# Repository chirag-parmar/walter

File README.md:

# Walter: The Water Butler

> Proof of concept document can be found [here](docs/POC.md)

### Dependencies: *(Tested on MACOS)*

1. [Download](https://www.nordicsemi.com/Software-and-tools/Software/nRF5-SDK/Download) nRF5 SDK
2. [Download](https://developer.arm.com/tools-and-software/open-source-software/developer-tools/gnu-toolchain/gnu-rm/downloads) ARM GCC toolchain
4. [Download](https://www.nordicsemi.com/Software-and-Tools/Development-Tools/nRF-Command-Line-Tools/Download#infotabs) nRF5x Command Line Tools.
4. Extract nRF5 SDK and rename the extracted folder to `nrf5-sdk`.
5. Extract GCC ARM toolchain and rename the extracted folder to `arm-toolchain`
6. Extract `nRF5x Command Line Tools` TAR file.
    * Navigate inside the nrf ommand line tools folder and install the Jlink package withing it.
    * Navigate inside the nrf ommand line tools folder and install the `nRF5x Command Line Tools` package withing it.
7. Check installations
    * J-Link *(MAC-OS)*: Check if this path exists `/Applications/SEGGER/JLink`
    * nRF5x Command Line Tools: `nrfjprog -v` must output the version.
8. Export Environment variables to specifying SDK folder path and ARM toolchain path.
    * `export SDK_ROOT=<PATH TO nrf5-sdk/ folder>`
    * `export GNU_INSTALL_ROOT=<PATH TO arm-toolchain/bin/ folder>`

> MAC-OS Complications: The system is going to complain that "the developer cannot be verified" for `arm-none-eabi-gcc`, `cc1`, `as`, `collect2`, `ld`, `liblto_plugin.0.so`, `arm-none-eabi-size`, `arm-none-eabi-objcopy`. Click on `Cancel` and then open Security and Privacy settings and click on `Allow Anyway`. These complains are gonna show one after the another.

### Burning the software:
```bash
make flash
```

### TODO:
* [x] [IMPORTANT] Debug NRF52840 - doesn't stop advertising at all
* [x] [IMPORTANT] initialize GPIO only while reading the sensor.
* [x] [IMPORTANT] Debug app: after refresh or after close and restart of app BLE shows connected but not re4ading notifications - most probably it is the BleManager object that has gone out of scope.
* [ ] README Documentation
  * [ ] NRF softdevice and flashing instructions without debugger and with debugger 
* [ ] Statistical and Analytical
  * [ ] function for analysing a day's worth of data and extracting the num. of bottles drank metric
  * [ ] triggers for interacting with the user
  * [ ] Touch sensing
* [ ] Software
  * [ ] Using NRF52840 Dongle.
    * [x] Port Capcitive Sensor library to nRF
    * [x] Define BLE services and characteristics
    * [ ] Finish battery level indication integration (depends on power supply design)
  * [x] App Design
    * [x] POC integration with BLE
    * [x] UI Wire Frame
    * [x] UI Design and Integration with BLE
    * [x] run ble recorded in background
    * [x] save data locally - ~~use firebase~~
      * [x] save device info
      * [x] save readings
      * [x] save calibration values
      * [x] save settings
      * [x] save on change
    * [x] Main screen statistics design
* [ ] Hardware
  * [ ] Sensor fabrication documentation
  * [ ] hardware fabrication documentation
  * [x] ~~Aluminium or Copper Tape electrodes~~ - didn't try but shouldn't be too different
  * [x] ~~3D printed case~~ - Going with no case design. who cares about the case anyway. The board is waterproofed
  * [x] Power supply design
    * [x] Coin Cells/ Super Capacitors - Super capacitor can power only for 6 minutes
      * [x] Investigate if we can use coin cells/super capacitors
      * [x] Calculate the usage time per charge and choose an appropriately sized battery
      * [x] Design necessary circuitry for using coin/cell or supercapcitors
      * [x] Fabricate and Integrate circuitry and battery with nrf52840

### Power Caclulations for Supercapacitor

Current draw - 11uA for 8 s and 3 ma for 2s => ~600uA (average)
Power Consumption at 3.6v = 3.6v * 600uA => 2.16mW

Energy stored in the capacitor = 1/2*C*deltaV*deltaV = 0.5 * 1F * (3.6v- 2v)^2 = 1.28J Joules

Energy = Power * Time => Time = Energy/Power => 1.28J/2.16mW => 592s => ~10minutes

**Decision:** Use CR2032 or better rechargeable CR2032

### Future Ideas:

* [ ] onboarding flow
* [ ] social - share water usage statistics with a friend, challenges etc.
* [ ] better UI

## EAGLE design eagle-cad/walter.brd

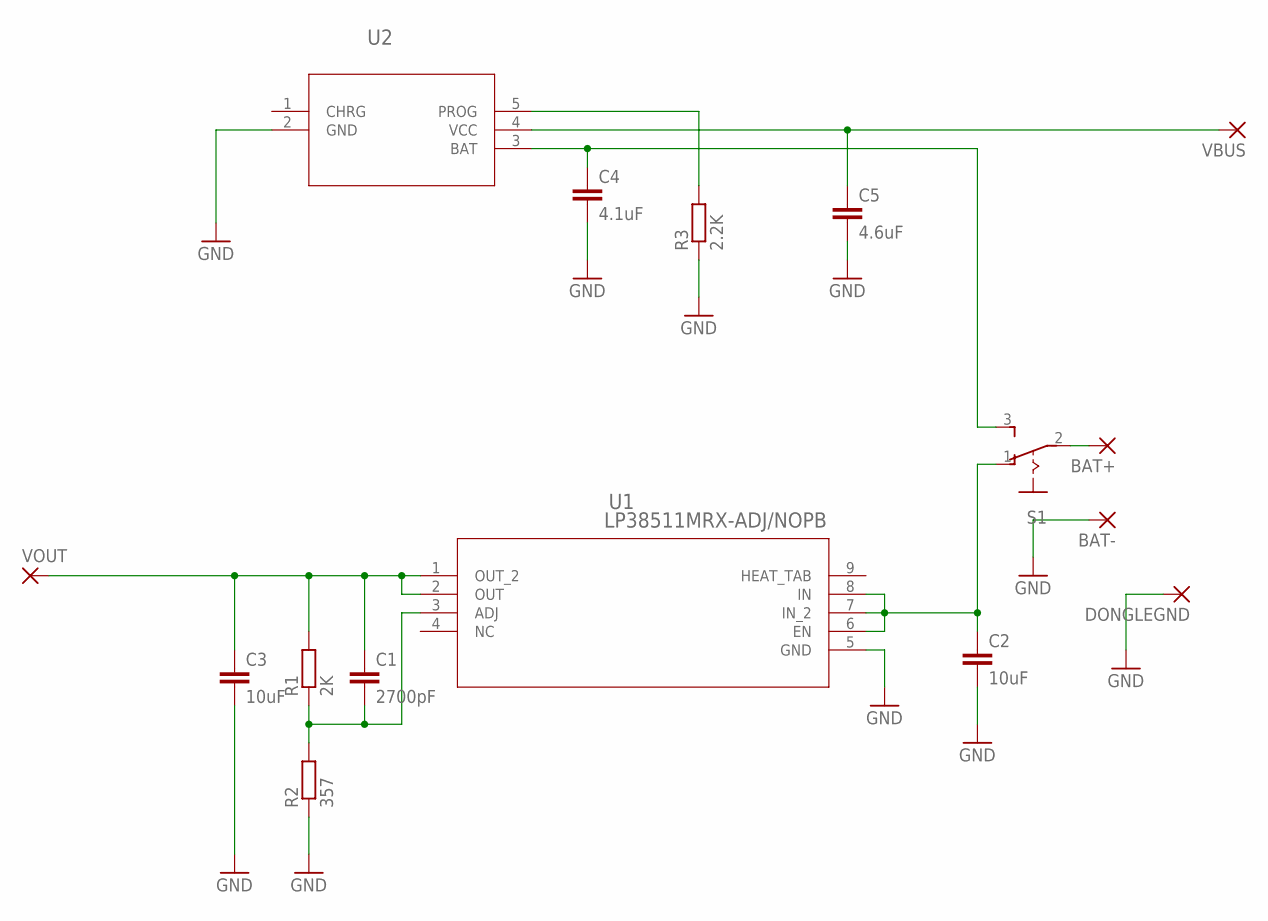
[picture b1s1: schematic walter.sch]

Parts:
BAT+: 1,6/0,8
BAT-: 1,6/0,8
C1: 2700pF; C0402
C2, C3: 10uF; C0603
C4: 4.1uF; C0603
C5: 4.6uF; C0603
DONGLEGND: 1,6/0,8
R1: 2K; R0402
R2: 357; R0603
R3: 2.2K; R0603
S1: 255SB
U1: LP38511MRX-ADJ/NOPB; MRA08B_TEX
U2: LTC4054LES5-4.2TRPBF; S_5_ADI
VBUS: 1,6/0,8
VOUT: 1,6/0,8

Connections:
GND: BAT-.1, C2.2, C3.2, C4.2, C5.2, DONGLEGND.1, R2.1, R3.1, U1.5 (GND), U2.2 (GND)
unnamed: C2.1, S1.1 (O), U1.6 (EN), U1.7 (IN_2), U1.8 (IN)
unnamed: C4.1, S1.3 (S), U2.3 (BAT)
unnamed: C1.1, C3.1, R1.2, U1.1 (OUT_2), U1.2 (OUT), VOUT.1
unnamed: C1.2, R1.1, R2.2, U1.3 (ADJ)
unnamed: BAT+.1, S1.2
unnamed: R3.2, U2.5 (PROG)
unnamed: C5.1, U2.4 (VCC), VBUS.1

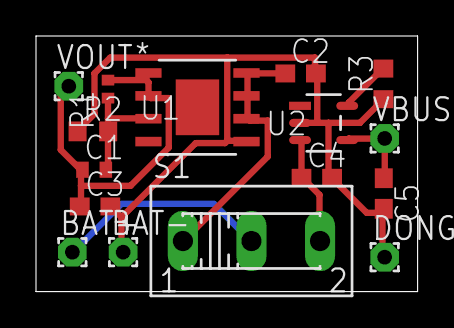
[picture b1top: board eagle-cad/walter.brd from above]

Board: 2 copper layers, 21.2 x 14.2 mm, 16 parts (0 on the bottom side), 8 nets.

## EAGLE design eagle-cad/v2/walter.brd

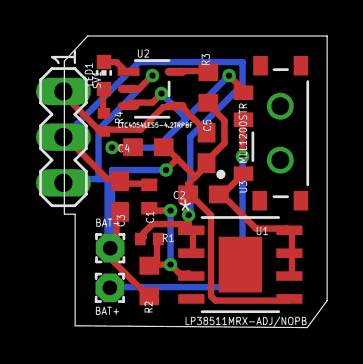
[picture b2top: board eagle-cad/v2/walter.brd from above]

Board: 2 copper layers, 14.6 x 16.2 mm, 16 parts (0 on the bottom side), 10 nets.

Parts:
BAT+: 1,6/0,8
BAT-: 1,6/0,8
C1: 2700pF; C0402
C2, C3: 10uF; C0603
C4: 4.1uF; C0603
C5: 4.6uF; C0603
LED1: CHIP-LED0603
R1: 2K; R0402
R2: 357; R0603
R3: 2.2K; R0603
R4: lim; R0402
SV1: MA03-1
U1: LP38511MRX-ADJ/NOPB; MRA08B_TEX
U2: LTC4054LES5-4.2TRPBF; S_5_ADI
U3: MLL1200STR; SW_MLL1200STR_TEC

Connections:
GND: BAT-.1, C2.2, C3.2, C4.2, C5.2, R2.1, R3.1, SV1.3, U1.5, U2.2
unnamed: C2.1, U1.6, U1.7, U1.8, U3.1
unnamed: C4.1, U2.3, U3.3
unnamed: C1.1, C3.1, R1.2, SV1.2, U1.1, U1.2
unnamed: C1.2, R1.1, R2.2, U1.3
unnamed: BAT+.1, U3.2
unnamed: R3.2, U2.5
unnamed: C5.1, R4.2, SV1.1, U2.4
unnamed: LED1.A, R4.1
unnamed: LED1.C, U2.1

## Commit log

2020-07-11 init
2020-07-12 walter class
2020-07-12 script for creating datasets
2020-07-12 better async for dataset keyboard key press
2020-07-12 fix continue and replce with pass
2020-07-12 add filling property in datapoint
2020-07-12 update arduino code
2020-07-12 add linear and exponential filling datasets
2020-07-12 continuous filling dataset
2020-07-12 plotting
2020-07-12 dataset statistics calculator
2020-07-12 moving average statistics
2020-07-12 remove print from moving average func
2020-07-12 serial monitor code
2020-07-12 arduino code for moving average
2020-07-12 readme init with TODO
2020-07-14 images and circuit diagram
2020-07-14 add requirements.txt
2020-07-14 add images to readme
2020-07-14 add basic instructions
2020-07-14 add completion of moving average filter in TODO
2020-07-15 Create LICENSE
2020-07-15 update readme with the science of walter
2020-07-15 update README with data extraction process
2020-07-15 quick fix
2020-07-15 resize image
2020-07-15 readme changes
2020-07-15 cleaned linear incremental filling dataset
2020-07-15 remove unwanted datasets
2020-07-15 better method to collect data
2020-07-15 modify datasets to match the new method of dataset creation
2020-07-15 use plotly for graphing the datasets
2020-07-15 snapshot graphs into png
2020-07-15 remove old dataset plot
2020-07-15 update readme with statistics
2020-07-21 remove keyboard.py
2020-07-21 replace wrong dataset with correct dataset
2020-07-21 change statistics.py to adapt to new dataset structure
2020-07-21 remove keyboard dependency
2020-07-21 option to show graph without error range
2020-07-21 touch sensing
2020-07-22 voltage regulator datasheet added
2020-07-22 move python scripts inside scripts folder
2020-07-22 nrf template project
2020-07-22 readme update for nrf
2020-07-25 touch sensing library ported into nrf
2020-07-25 add sub steps for improvements
2020-07-26 eagle schematics
2020-07-26 remove datasheets
2020-07-30 remove eagle-cad
2020-07-30 re-add eagle-cad
2020-08-15 move arduino code to it's own folder
2020-09-15 schematics update
2020-09-16 copy ble template from sdk
2020-09-17 custom ble service template
2020-09-17 debug scripts
2020-09-20 v2 regulator board
2020-09-20 board routing layout fixes
2021-07-13 add sdk to vs code
2021-07-13 move uuids to scan response message
2021-07-13 walter ble service and charcteristic definitions
2021-07-13 characteristic update
2021-07-13 send value only when notify flag is set by client
2021-07-13 integrate with sensor
2021-07-14 documentation update
2021-07-15 connection error fixed
2021-07-16 loop timing factor adjustment
2021-07-16 remove alternate capsense library
2021-07-16 1. connected led off 2. fix notif data send
2021-07-18 use capsense driver from nrf
2021-07-20 use github example
2021-07-22 working
2021-07-22 archive
2021-07-22 archive fix
2021-07-22 app init
2021-07-22 re-organize
2021-07-24 basics of ble done
2021-07-25 Blinking animation and lot more
2021-07-25 organize code into different logical sections
2021-07-25 new screen transition
2021-07-25 water level animation
2021-07-26 Water level animations finished
2021-07-26 calibration mechanism done
2021-07-26 app signing
2021-07-26 todo
2021-07-27 settings screen
2021-07-30 remove dependency of ble using eventemitter
2021-07-31 secondary screens as modals
2021-07-31 background fix for ble screen
2021-07-31 remove unnecessary console.logs
2021-08-28 read me update
2021-10-08 power mgmt init commit
2022-01-02 enable RTT backend and logging
2022-01-02 add log before sleep
2022-01-24 power_optimization
2022-01-27 readme update
2022-01-27 small ux fixes
2022-01-28 refactor and ui cleanup
2022-01-28 Configuration screen finsihed
2022-01-28 save configurations and settings
2022-01-28 fix notify bugs
2022-01-28 icon mismatch fix
2022-01-28 update progress
2022-01-28 ble over app lifecycle
2022-01-28 fixes
2022-01-28 Bump tmpl from 1.0.4 to 1.0.5 in /app/Walter
    Bumps [tmpl](https://github.com/daaku/nodejs-tmpl) from 1.0.4 to 1.0.5.
    - [Release notes](https://github.com/daaku/nodejs-tmpl/releases)
    - [Commits](https://github.com/daaku/nodejs-tmpl/commits/v1.0.5)
    ---
    updated-dependencies:
    - dependency-name: tmpl
2022-01-28 Bump shelljs from 0.8.4 to 0.8.5 in /app/Walter
    Bumps [shelljs](https://github.com/shelljs/shelljs) from 0.8.4 to 0.8.5.
    - [Release notes](https://github.com/shelljs/shelljs/releases)
    - [Changelog](https://github.com/shelljs/shelljs/blob/master/CHANGELOG.md)
    - [Commits](https://github.com/shelljs/shelljs/compare/v0.8.4...v0.8.5)
    ---
    updated-dependencies:
2022-01-28 Bump node-fetch from 2.6.1 to 2.6.7 in /app/Walter
    Bumps [node-fetch](https://github.com/node-fetch/node-fetch) from 2.6.1 to 2.6.7.
    - [Release notes](https://github.com/node-fetch/node-fetch/releases)
    - [Commits](https://github.com/node-fetch/node-fetch/compare/v2.6.1...v2.6.7)
    ---
    updated-dependencies:
    - dependency-name: node-fetch
2022-03-02 Bump plist from 3.0.2 to 3.0.4 in /app/Walter
    Bumps [plist](https://github.com/TooTallNate/node-plist) from 3.0.2 to 3.0.4.
    - [Release notes](https://github.com/TooTallNate/node-plist/releases)
    - [Changelog](https://github.com/TooTallNate/plist.js/blob/master/History.md)
    - [Commits](https://github.com/TooTallNate/node-plist/commits)
    ---
    updated-dependencies:
2022-03-30 Bump minimist from 1.2.5 to 1.2.6 in /app/Walter
    Bumps [minimist](https://github.com/substack/minimist) from 1.2.5 to 1.2.6.
    - [Release notes](https://github.com/substack/minimist/releases)
    - [Commits](https://github.com/substack/minimist/compare/1.2.5...1.2.6)
    ---
    updated-dependencies:
    - dependency-name: minimist
2022-04-29 Bump async from 2.6.3 to 2.6.4 in /app/Walter
    Bumps [async](https://github.com/caolan/async) from 2.6.3 to 2.6.4.
    - [Release notes](https://github.com/caolan/async/releases)
    - [Changelog](https://github.com/caolan/async/blob/v2.6.4/CHANGELOG.md)
    - [Commits](https://github.com/caolan/async/compare/v2.6.3...v2.6.4)
    ---
    updated-dependencies:
2022-06-02 Bump simple-plist from 1.1.1 to 1.3.1 in /app/Walter
    Bumps [simple-plist](https://github.com/wollardj/simple-plist) from 1.1.1 to 1.3.1.
    - [Release notes](https://github.com/wollardj/simple-plist/releases)
    - [Commits](https://github.com/wollardj/simple-plist/compare/v1.1.1...v1.3.1)
    ---
    updated-dependencies:
    - dependency-name: simple-plist
2022-10-12 Bump xmldom and plist in /app/Walter
    Removes [xmldom](https://github.com/xmldom/xmldom). It's no longer used after updating ancestor dependency [plist](https://github.com/TooTallNate/node-plist). These dependencies need to be updated to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
    Removes `xmldom`
    Updates `plist` from 3.0.2 to 3.0.6
    - [Release notes](https://github.com/TooTallNate/node-plist/releases)
    - [Changelog](https://github.com/TooTallNate/plist.js/blob/master/History.md)
    - [Commits](https://github.com/TooTallNate/node-plist/commits)
2022-11-11 Bump minimatch from 3.0.4 to 3.1.2 in /app/Walter
    Bumps [minimatch](https://github.com/isaacs/minimatch) from 3.0.4 to 3.1.2.
    - [Release notes](https://github.com/isaacs/minimatch/releases)
    - [Commits](https://github.com/isaacs/minimatch/compare/v3.0.4...v3.1.2)
    ---
    updated-dependencies:
    - dependency-name: minimatch
2022-12-07 Bump decode-uri-component from 0.2.0 to 0.2.2 in /app/Walter
    Bumps [decode-uri-component](https://github.com/SamVerschueren/decode-uri-component) from 0.2.0 to 0.2.2.
    - [Release notes](https://github.com/SamVerschueren/decode-uri-component/releases)
    - [Commits](https://github.com/SamVerschueren/decode-uri-component/compare/v0.2.0...v0.2.2)
    ---
    updated-dependencies:
    - dependency-name: decode-uri-component
2023-01-07 Bump json5 from 2.2.0 to 2.2.3 in /app/Walter
    Bumps [json5](https://github.com/json5/json5) from 2.2.0 to 2.2.3.
    - [Release notes](https://github.com/json5/json5/releases)
    - [Changelog](https://github.com/json5/json5/blob/main/CHANGELOG.md)
    - [Commits](https://github.com/json5/json5/compare/v2.2.0...v2.2.3)
    ---
    updated-dependencies:
2023-02-08 Bump @sideway/formula from 3.0.0 to 3.0.1 in /app/Walter
    Bumps [@sideway/formula](https://github.com/sideway/formula) from 3.0.0 to 3.0.1.
    - [Release notes](https://github.com/sideway/formula/releases)
    - [Commits](https://github.com/sideway/formula/compare/v3.0.0...v3.0.1)
    ---
    updated-dependencies:
    - dependency-name: "@sideway/formula"
2023-03-06 Bump minimist from 1.2.5 to 1.2.8 in /app/Walter
    Bumps [minimist](https://github.com/minimistjs/minimist) from 1.2.5 to 1.2.8.
    - [Release notes](https://github.com/minimistjs/minimist/releases)
    - [Changelog](https://github.com/minimistjs/minimist/blob/main/CHANGELOG.md)
    - [Commits](https://github.com/minimistjs/minimist/compare/v1.2.5...v1.2.8)
    ---
    updated-dependencies:

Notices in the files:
parts and their libraries:
COPYRIGHT: Copyright (C) 2016 Accelerated Designs. All rights reserved
COPYRIGHT: Copyright (C) 2018 Accelerated Designs. All rights reserved
